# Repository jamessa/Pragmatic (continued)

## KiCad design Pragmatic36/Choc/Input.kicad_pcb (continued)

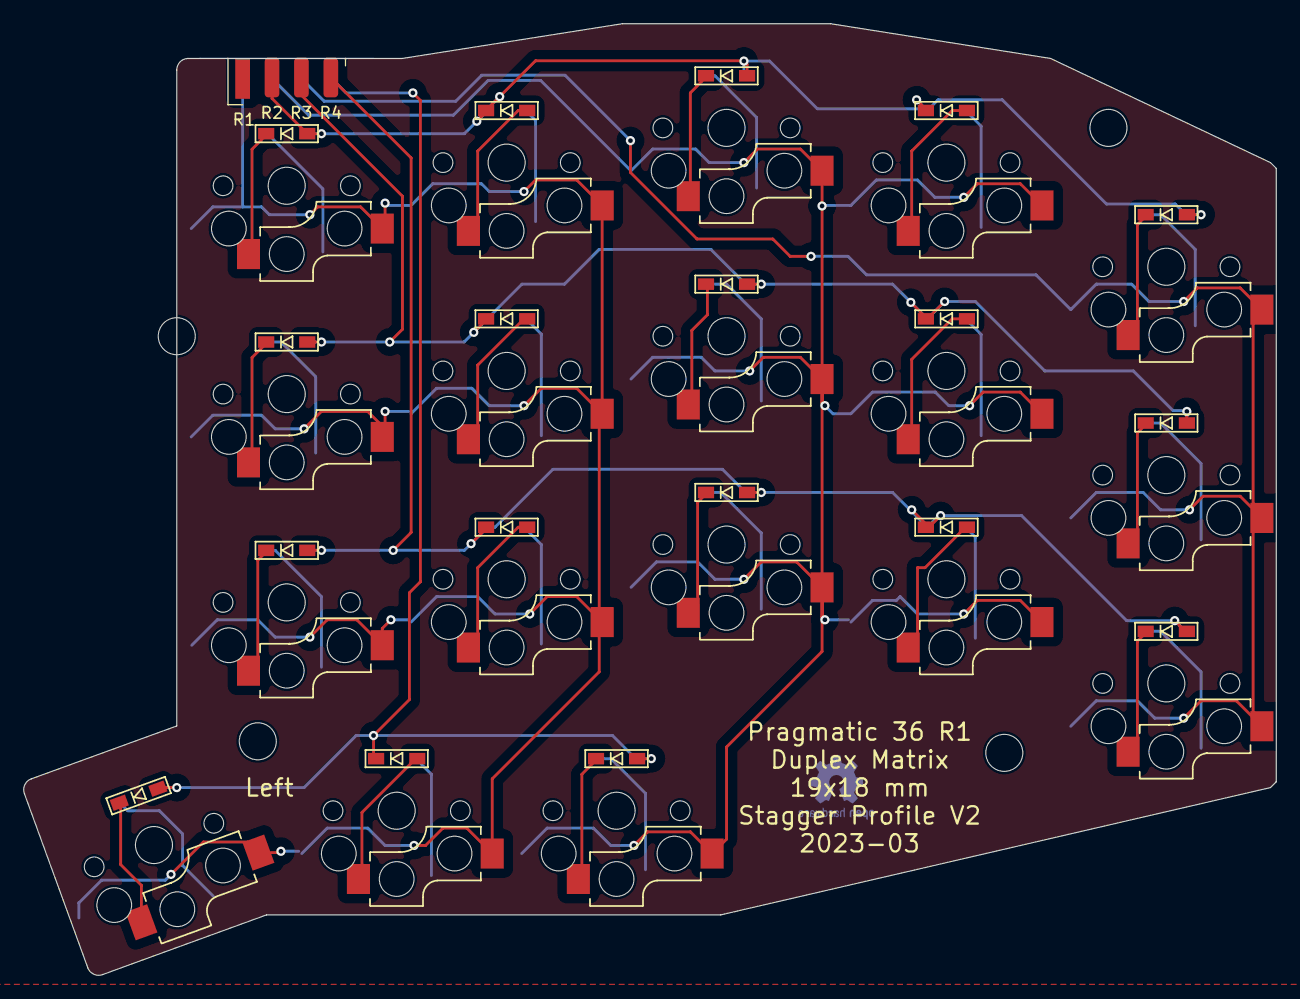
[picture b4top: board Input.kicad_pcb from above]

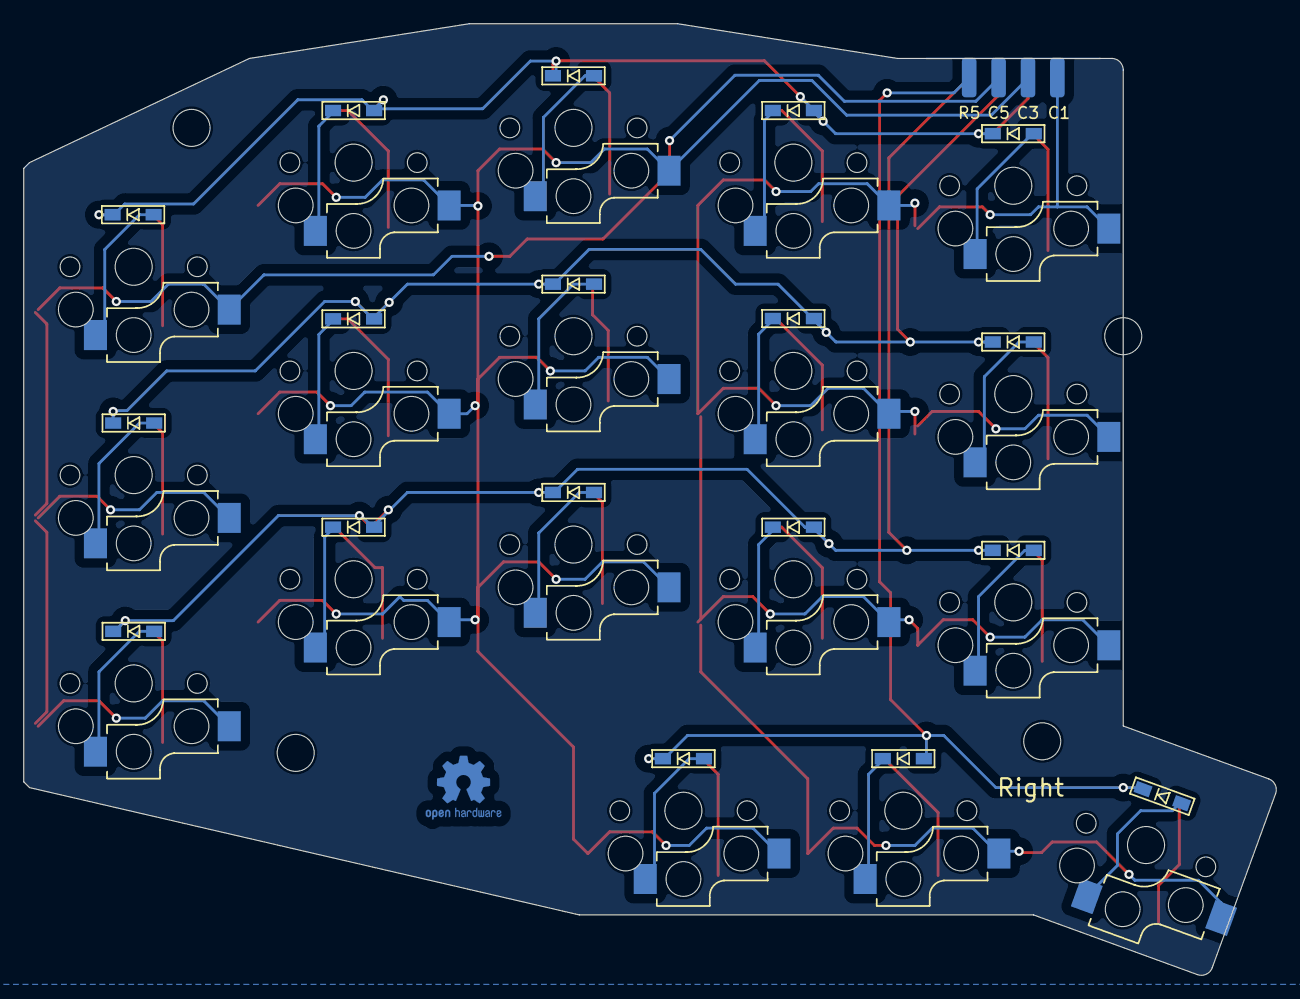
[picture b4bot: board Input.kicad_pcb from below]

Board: 2 copper layers, 108.2 x 82.2 mm, 77 parts (36 on the bottom side), 43 nets.
